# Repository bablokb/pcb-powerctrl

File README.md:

pcb-powerctrl
=============

This project contains the KiCAD-project-files for a  small pcb with touchpads
and drill holes for 5,5/2,1 sockets. The KiCAD-sources are in the sub-directory
[pcb-powerctrl](pcb-powerctrl), production-files with gerber-layers and drill-hole files are
in the sub-directory [production](production).

Schematic
---------

Layout
------

3D-View
-------

License
-------

Shield: [![CC BY-SA 4.0][cc-by-sa-shield]][cc-by-sa]

This work is licensed under a
[Creative Commons Attribution-ShareAlike 4.0 International
License][cc-by-sa].

[![CC BY-SA 4.0][cc-by-sa-image]][cc-by-sa]

[cc-by-sa]: http://creativecommons.org/licenses/by-sa/4.0/
[cc-by-sa-image]: https://licensebuttons.net/l/by-sa/4.0/88x31.png
[cc-by-sa-shield]:
https://img.shields.io/badge/License-CC%20BY--SA%204.0-lightgrey.svg

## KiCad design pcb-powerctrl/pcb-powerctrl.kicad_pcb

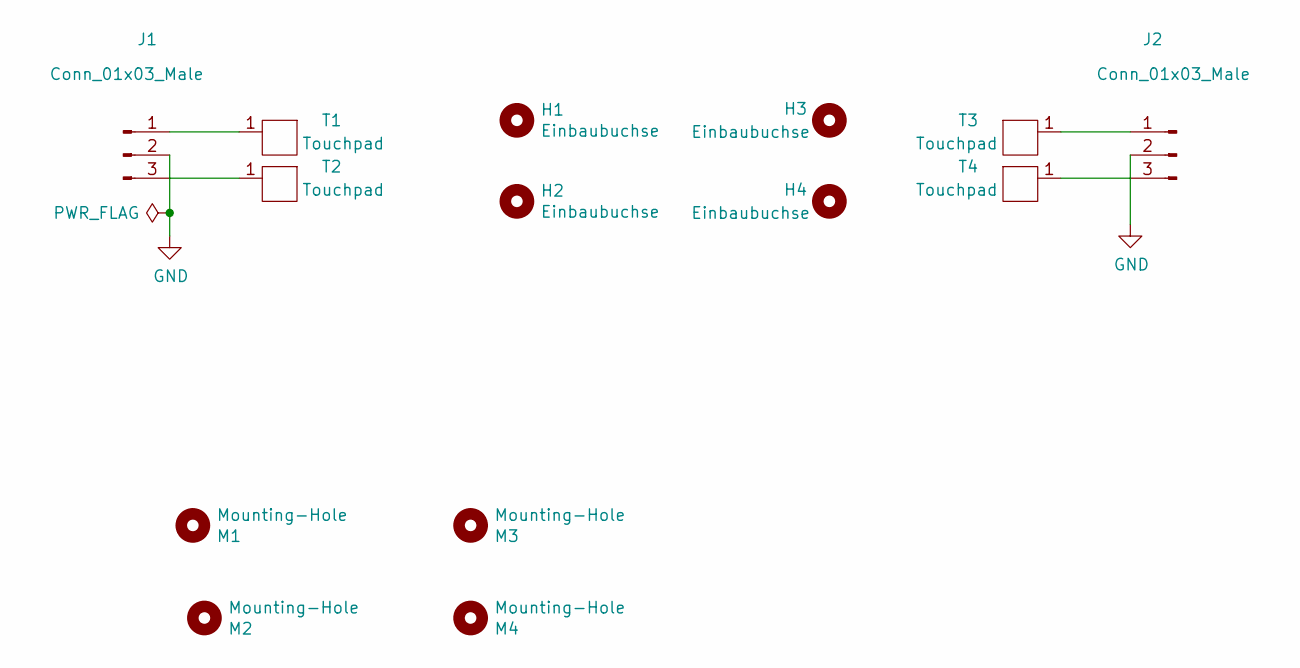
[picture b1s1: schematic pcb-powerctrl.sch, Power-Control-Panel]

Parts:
H1, H2, H3, H4: Einbaubuchse; Einbaubuchse_55x21
J1, J2: Conn_01x03_Male; PinHeader_1x03_P2.54mm_Vertical
M1, M2, M3, M4: Mounting-Hole; MountingHole_2.5mm
T1, T2, T3, T4: Touchpad

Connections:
GND: J1.2, J2.2
unnamed: J1.1, T1.1
unnamed: J1.3, T2.1
unnamed: J2.1, T3.1
unnamed: J2.3, T4.1

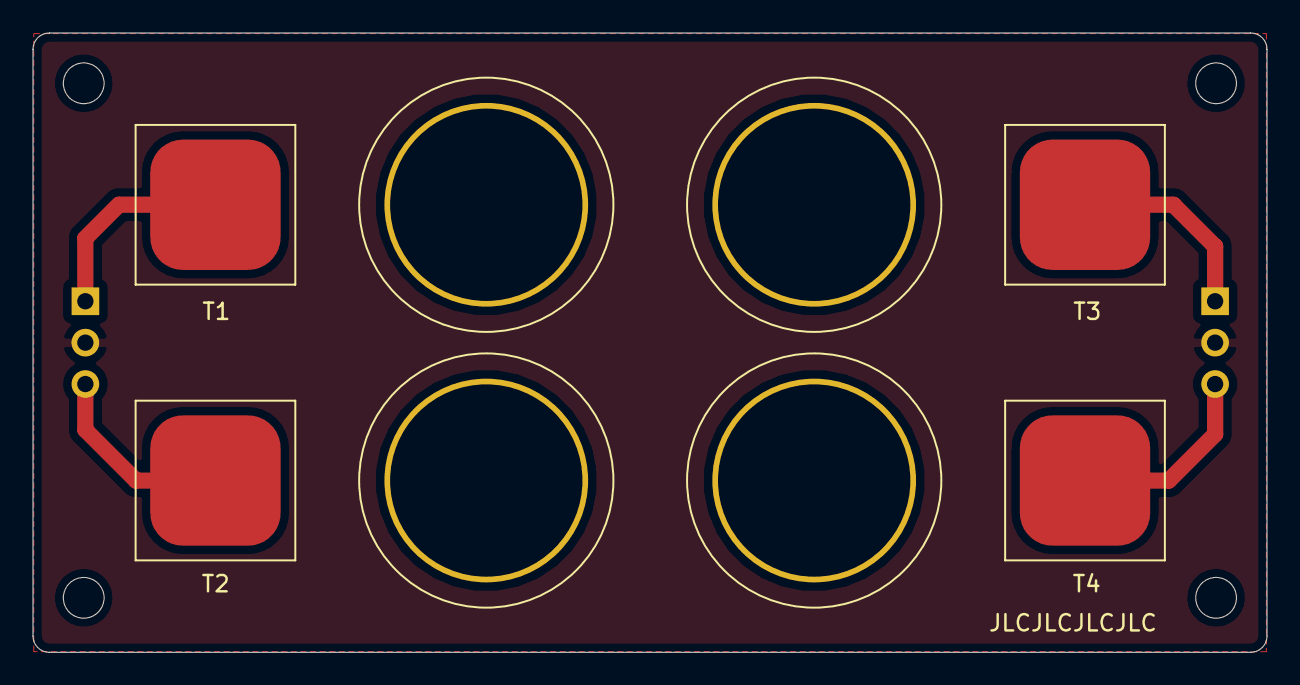
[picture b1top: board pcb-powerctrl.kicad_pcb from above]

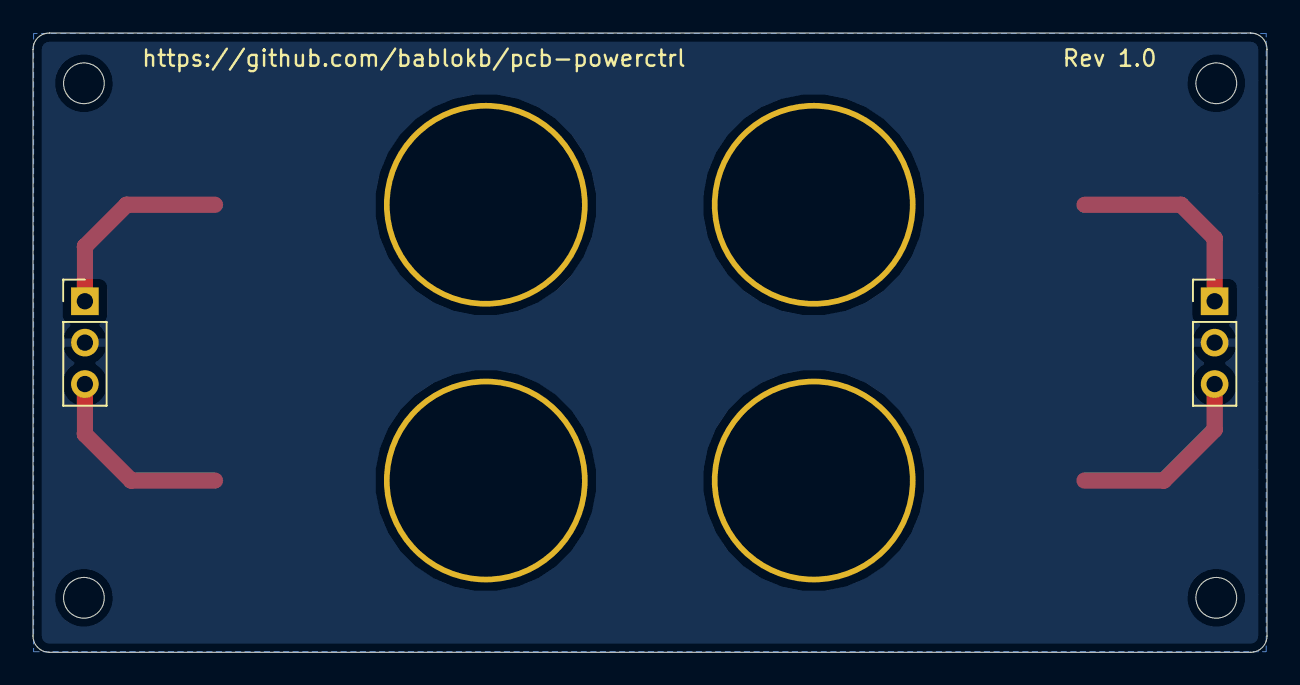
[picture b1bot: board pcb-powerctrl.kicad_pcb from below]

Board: 2 copper layers, 75.7 x 38.0 mm, 14 parts (2 on the bottom side), 5 nets.

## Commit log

2021-06-04 added desciption
2021-10-30 added section about license
